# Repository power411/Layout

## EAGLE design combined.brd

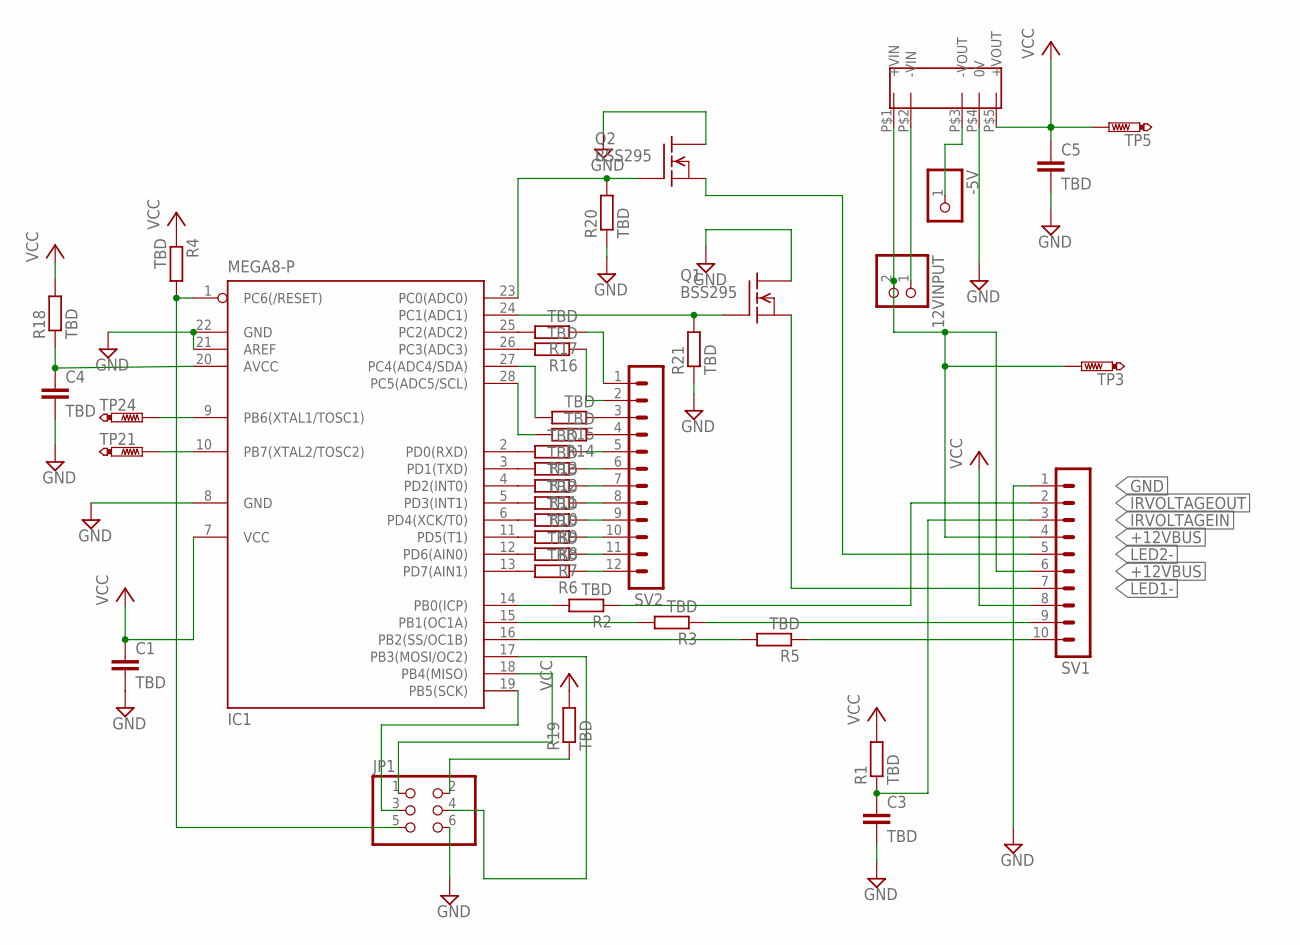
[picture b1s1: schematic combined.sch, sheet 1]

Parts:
12VINPUT: PINHD-1X2; 1X02
-5V: PINHD-1X1; 1X01
C1, C3, C4, C5: TBD; C0805
IC1: MEGA8-P; DIL28-3
JP1: PINHD-2X3; 2X03
Q1, Q2: BSS295; TO92
R1, R2, R3, R4, R5, R6, R7, R8, R9, R10, R11, R12, R13, R14, R15, R16, R17, R18, R19, R20, R21: TBD; R0805
SV1: MA10-1
SV2: MA12-1
TP3, TP5, TP21, TP24: PTR1B1,27; B1,27
U$1: NKA1205SC

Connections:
0VBUS: 12VINPUT.1, U$1.P$2 (-VIN)
+12VBUS: 12VINPUT.2, SV1.4, SV1.6, TP3.TP, U$1.P$1 (+VIN)
GND: C1.2, C3.2, C4.2, C5.2, IC1.8 (GND), IC1.21 (AREF), IC1.22 (GND), JP1.6, Q1.2 (D), Q2.2 (D), R20.1, R21.1, SV1.1, U$1.P$4 (0V); also elsewhere on the board
IRVOLTAGEIN: C3.1, R1.1, SV1.3
IRVOLTAGEOUT: R2.1, SV1.2
LED1-: Q1.3 (S), SV1.7
LED2-: Q2.3 (S), SV1.5
unnamed: IC1.24 (PC1(ADC1)), Q1.1 (G), R21.2
unnamed: R3.1, SV1.9
unnamed: R17.1, SV2.1
unnamed: R16.1, SV2.2
unnamed: IC1.17 (PB3(MOSI/OC2)), JP1.4
unnamed: IC1.27 (PC4(ADC4/SDA)), R15.2
unnamed: IC1.28 (PC5(ADC5/SCL)), R14.2
unnamed: IC1.23 (PC0(ADC0)), Q2.1 (G), R20.2
unnamed: R5.1, SV1.10
unnamed: R13.1, SV2.5
unnamed: IC1.14 (PB0(ICP)), R2.2
unnamed: R12.1, SV2.6
unnamed: R11.1, SV2.7
unnamed: R10.1, SV2.8
unnamed: R9.1, SV2.9
unnamed: R8.1, SV2.10
unnamed: R7.1, SV2.11
unnamed: IC1.15 (PB1(OC1A)), R3.2
unnamed: IC1.16 (PB2(SS/OC1B)), R5.2
unnamed: R6.1, SV2.12
unnamed: IC1.25 (PC2(ADC2)), R17.2
unnamed: IC1.26 (PC3(ADC3)), R16.2
unnamed: R15.1, SV2.3
unnamed: R14.1, SV2.4
unnamed: IC1.2 (PD0(RXD)), R13.2
unnamed: IC1.6 (PD4(XCK/T0)), R9.2
unnamed: IC1.18 (PB4(MISO)), JP1.1
unnamed: IC1.19 (PB5(SCK)), JP1.3
unnamed: IC1.9 (PB6(XTAL1/TOSC1)), TP24.TP
unnamed: IC1.10 (PB7(XTAL2/TOSC2)), TP21.TP
unnamed: IC1.11 (PD5(T1)), R8.2
unnamed: IC1.12 (PD6(AIN0)), R7.2
unnamed: IC1.1 (PC6(/RESET)), JP1.5, R4.2
unnamed: IC1.13 (PD7(AIN1)), R6.2
unnamed: IC1.3 (PD1(TXD)), R12.2
unnamed: IC1.4 (PD2(INT0)), R11.2
unnamed: IC1.5 (PD3(INT1)), R10.2
unnamed: C4.1, IC1.20 (AVCC), R18.1
unnamed: JP1.2, R19.1
unnamed: -5V.1, U$1.P$3 (-VOUT)
VCC: C1.1, C5.1, IC1.7 (VCC), R1.2, R4.1, R18.2, R19.2, SV1.8, TP5.TP, U$1.P$5 (+VOUT); also elsewhere on the board

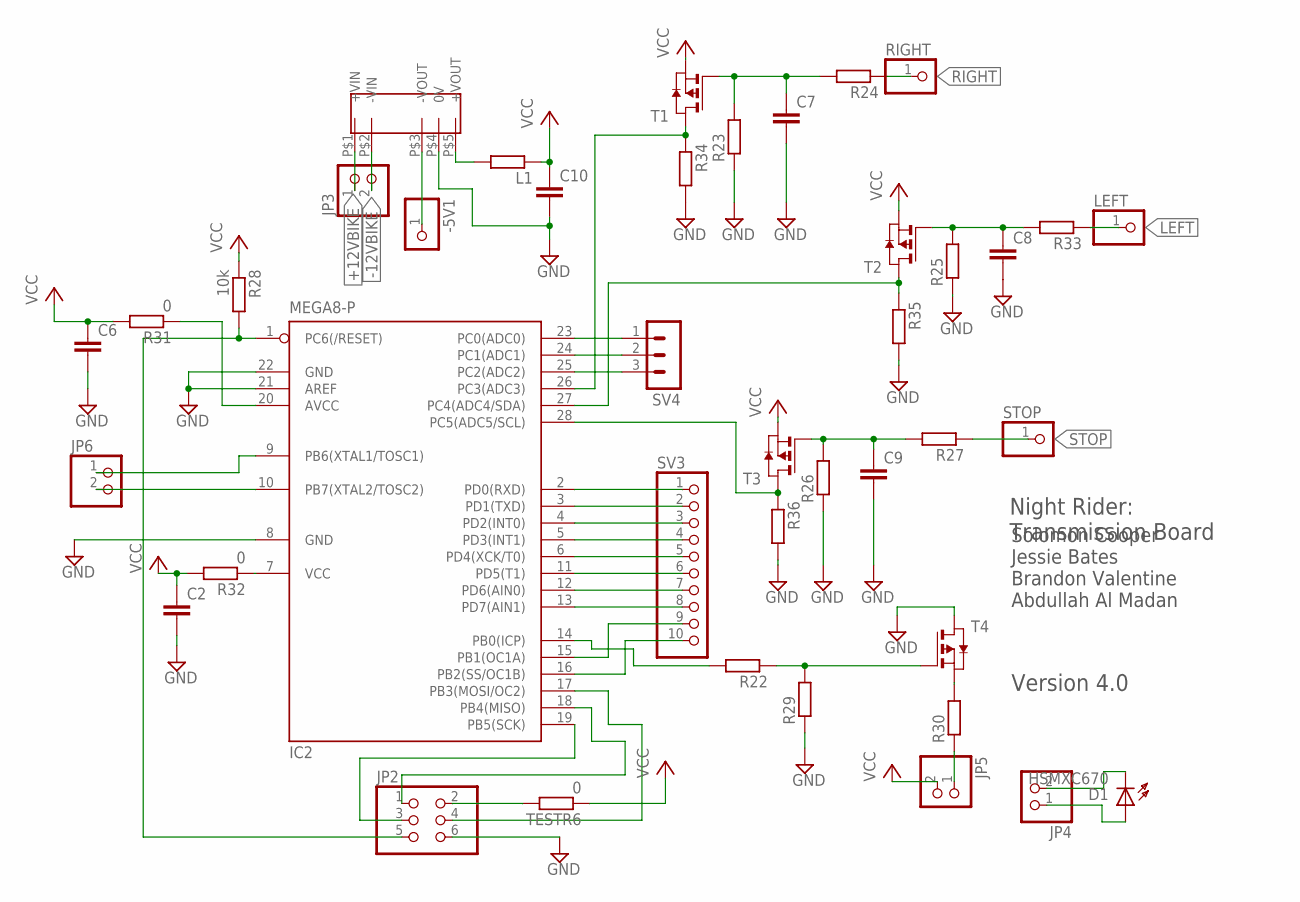
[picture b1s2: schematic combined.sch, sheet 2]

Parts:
-5V1: PINHD-1X1; 1X01
C2, C6, C7, C8, C9, C10: C-EUC0805; C0805
D1: HSMXC670
IC2: MEGA8-P; DIL28-3
JP2: PINHD-2X3; 2X03
JP3, JP4, JP5, JP6: PINHD-1X2; 1X02
L1: R-EU_M0805; M0805
LEFT: PINHD-1X1; 1X01
R22, R23, R24, R25, R26, R27, R29, R30, R33, R34, R35, R36: R-EU_M0805; M0805
R28: 10k; M0805
R31, R32: 0; M0805
RIGHT: PINHD-1X1; 1X01
STOP: PINHD-1X1; 1X01
SV3: PINHD-1X10; 1X10
SV4: MA03-1
T1, T2, T3, T4: PMOSSOT23; SOT-23
TESTR6: 0; M0805
U$2: NKA1205SC

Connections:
+12VBIKE: JP3.1, U$2.P$1 (+VIN)
-12VBIKE: JP3.2, U$2.P$2 (-VIN)
GND: C2.2, C6.2, C7.2, C8.2, C9.2, C10.2, IC2.8 (GND), IC2.21 (AREF), IC2.22 (GND), JP2.6, R23.1, R25.1, R26.1, R29.1, R34.2, R35.2, R36.2, T4.1 (D), U$2.P$4 (0V); also elsewhere on the board
LEFT: LEFT.1, R33.1
unnamed: IC2.17 (PB3(MOSI/OC2)), JP2.4
unnamed: IC2.18 (PB4(MISO)), JP2.1
unnamed: IC2.19 (PB5(SCK)), JP2.3
unnamed: C8.1, R25.2, R33.2, T2.3 (G)
unnamed: C9.1, R26.2, R27.2, T3.3 (G)
unnamed: IC2.9 (PB6(XTAL1/TOSC1)), JP6.1
unnamed: IC2.1 (PC6(/RESET)), JP2.5, R28.2
unnamed: R22.1, R29.2, T4.3 (G)
unnamed: R30.2, T4.2 (S)
unnamed: IC2.23 (PC0(ADC0)), SV4.1
unnamed: IC2.24 (PC1(ADC1)), SV4.2
unnamed: IC2.25 (PC2(ADC2)), SV4.3
unnamed: IC2.7 (VCC), R32.1
unnamed: IC2.20 (AVCC), R31.1
unnamed: JP2.2, TESTR6.2
unnamed: IC2.10 (PB7(XTAL2/TOSC2)), JP6.2
unnamed: IC2.15 (PB1(OC1A)), SV3.9
unnamed: IC2.3 (PD1(TXD)), SV3.2
unnamed: IC2.4 (PD2(INT0)), SV3.3
unnamed: IC2.5 (PD3(INT1)), SV3.4
unnamed: IC2.6 (PD4(XCK/T0)), SV3.5
unnamed: IC2.11 (PD5(T1)), SV3.6
unnamed: IC2.12 (PD6(AIN0)), SV3.7
unnamed: IC2.13 (PD7(AIN1)), SV3.8
unnamed: IC2.16 (PB2(SS/OC1B)), SV3.10
unnamed: IC2.27 (PC4(ADC4/SDA)), R35.1, T2.1 (D)
unnamed: L1.2, U$2.P$5 (+VOUT)
unnamed: -5V1.1, U$2.P$3 (-VOUT)
unnamed: IC2.14 (PB0(ICP)), R22.2
unnamed: IC2.2 (PD0(RXD)), SV3.1
unnamed: C7.1, R23.2, R24.2, T1.3 (G)
unnamed: IC2.26 (PC3(ADC3)), R34.1, T1.1 (D)
unnamed: IC2.28 (PC5(ADC5/SCL)), R36.1, T3.1 (D)
unnamed: JP5.1, R30.1
unnamed: D1.K (C), JP4.2
unnamed: D1.A, JP4.1
RIGHT: R24.1, RIGHT.1
STOP: R27.1, STOP.1
VCC: C2.1, C6.1, C10.1, JP5.2, L1.1, R28.1, R31.2, R32.2, T1.2 (S), T2.2 (S), T3.2 (S), TESTR6.1; also elsewhere on the board

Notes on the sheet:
Night Rider: Transmission Board
Solomon Cooper Jessie Bates Brandon Valentine Abdullah Al Madan
Version 4.0

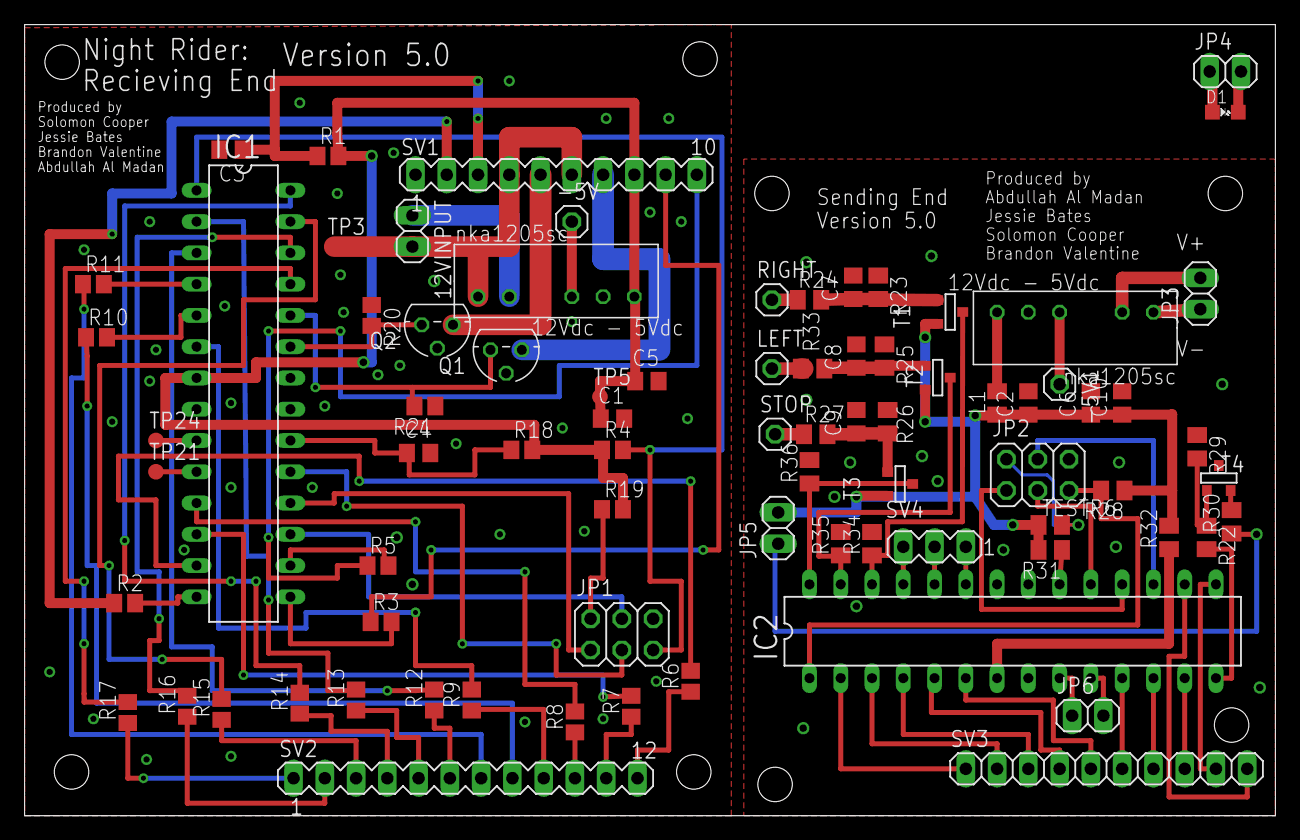
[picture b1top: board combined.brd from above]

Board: 2 copper layers, 101.6 x 64.3 mm, 79 parts (0 on the bottom side), 89 nets.

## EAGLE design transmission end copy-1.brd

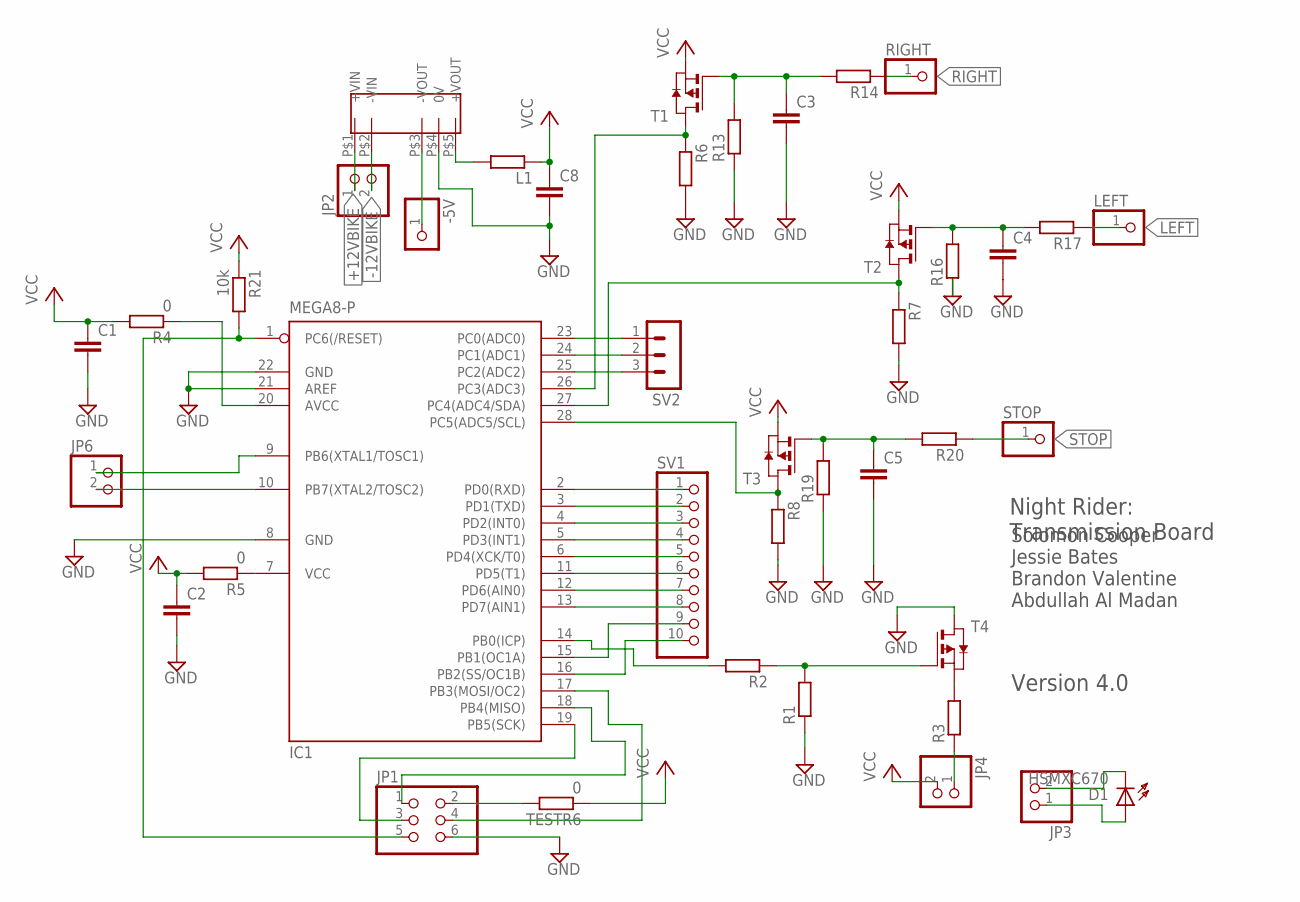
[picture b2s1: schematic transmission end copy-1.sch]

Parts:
-5V: PINHD-1X1; 1X01
C1, C2, C3, C4, C5, C8: C-EUC0805; C0805
D1: HSMXC670
IC1: MEGA8-P; DIL28-3
JP1: PINHD-2X3; 2X03
JP2, JP3, JP4, JP6: PINHD-1X2; 1X02
L1: R-EU_M0805; M0805
LEFT: PINHD-1X1; 1X01
R1, R2, R3, R6, R7, R8, R13, R14, R16, R17, R19, R20: R-EU_M0805; M0805
R4, R5: 0; M0805
R21: 10k; M0805
RIGHT: PINHD-1X1; 1X01
STOP: PINHD-1X1; 1X01
SV1: PINHD-1X10; 1X10
SV2: MA03-1
T1, T2, T3, T4: PMOSSOT23; SOT-23
TESTR6: 0; M0805
U$1: NKA1205SC

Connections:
+12VBIKE: JP2.1, U$1.P$1 (+VIN)
-12VBIKE: JP2.2, U$1.P$2 (-VIN)
GND: C1.2, C2.2, C3.2, C4.2, C5.2, C8.2, IC1.8 (GND), IC1.21 (AREF), IC1.22 (GND), JP1.6, R1.1, R6.2, R7.2, R8.2, R13.1, R16.1, R19.1, T4.1 (D), U$1.P$4 (0V)
LEFT: LEFT.1, R17.1
unnamed: IC1.2 (PD0(RXD)), SV1.1
unnamed: R1.2, R2.1, T4.3 (G)
unnamed: JP4.1, R3.1
unnamed: IC1.27 (PC4(ADC4/SDA)), R7.1, T2.1 (D)
unnamed: IC1.3 (PD1(TXD)), SV1.2
unnamed: R3.2, T4.2 (S)
unnamed: IC1.1 (PC6(/RESET)), JP1.5, R21.2
unnamed: IC1.14 (PB0(ICP)), R2.2
unnamed: L1.2, U$1.P$5 (+VOUT)
unnamed: IC1.4 (PD2(INT0)), SV1.3
unnamed: -5V.1, U$1.P$3 (-VOUT)
unnamed: IC1.9 (PB6(XTAL1/TOSC1)), JP6.1
unnamed: IC1.28 (PC5(ADC5/SCL)), R8.1, T3.1 (D)
unnamed: IC1.5 (PD3(INT1)), SV1.4
unnamed: IC1.6 (PD4(XCK/T0)), SV1.5
unnamed: IC1.11 (PD5(T1)), SV1.6
unnamed: IC1.12 (PD6(AIN0)), SV1.7
unnamed: IC1.13 (PD7(AIN1)), SV1.8
unnamed: D1.K (C), JP3.2
unnamed: IC1.15 (PB1(OC1A)), SV1.9
unnamed: IC1.16 (PB2(SS/OC1B)), SV1.10
unnamed: IC1.17 (PB3(MOSI/OC2)), JP1.4
unnamed: IC1.18 (PB4(MISO)), JP1.1
unnamed: IC1.19 (PB5(SCK)), JP1.3
unnamed: IC1.10 (PB7(XTAL2/TOSC2)), JP6.2
unnamed: IC1.23 (PC0(ADC0)), SV2.1
unnamed: IC1.24 (PC1(ADC1)), SV2.2
unnamed: IC1.25 (PC2(ADC2)), SV2.3
unnamed: IC1.26 (PC3(ADC3)), R6.1, T1.1 (D)
unnamed: IC1.7 (VCC), R5.1
unnamed: IC1.20 (AVCC), R4.1
unnamed: JP1.2, TESTR6.2
unnamed: C4.1, R16.2, R17.2, T2.3 (G)
unnamed: C3.1, R13.2, R14.2, T1.3 (G)
unnamed: D1.A, JP3.1
unnamed: C5.1, R19.2, R20.2, T3.3 (G)
RIGHT: R14.1, RIGHT.1
STOP: R20.1, STOP.1
VCC: C1.1, C2.1, C8.1, JP4.2, L1.1, R4.2, R5.2, R21.1, T1.2 (S), T2.2 (S), T3.2 (S), TESTR6.1

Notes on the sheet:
Night Rider: Transmission Board
Solomon Cooper Jessie Bates Brandon Valentine Abdullah Al Madan
Version 4.0

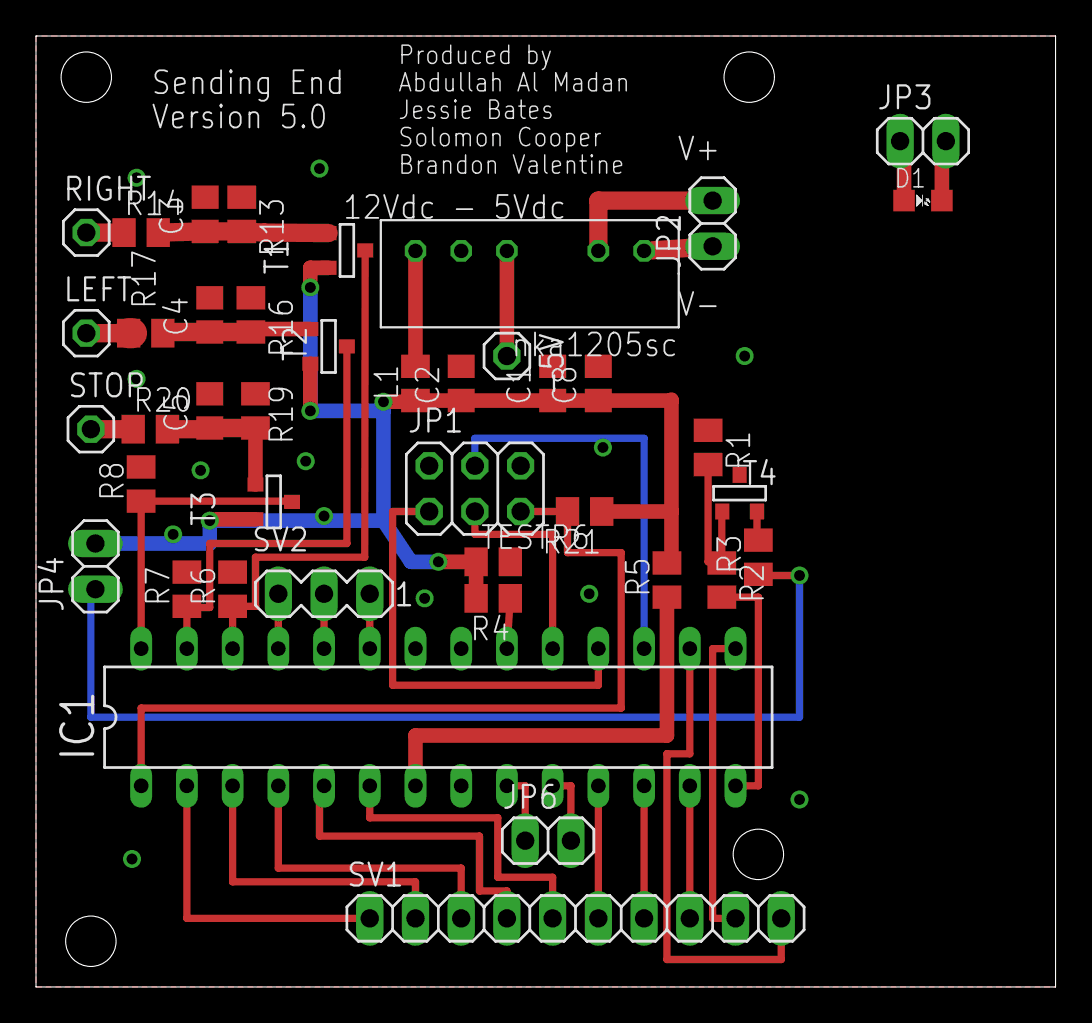
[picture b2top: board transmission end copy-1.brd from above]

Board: 2 copper layers, 56.6 x 52.8 mm, 41 parts (0 on the bottom side), 43 nets.

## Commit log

2012-11-19 fixing the layout of the PCB for the receiving and transmission end before sending them to Andrew to combine them
2012-11-19 in the transmission end, we fixed the design for the transistors for the diodes and the input signal, so it operates with PMOS transistors the way we want it. In the receiving end, we fixed the desig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
2012-11-19 The combined files are what Andrew helped on building for us
2012-11-19 the gerber file that we will submit to sunstone
